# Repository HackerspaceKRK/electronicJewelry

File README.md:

electronicJewelry
=================

Electronic jewelry made for workshops on TEDx Kraków 2013

Dependencies:
arm-none-eabi toolchain

CodeSourcery toolchain:
http://www.mentor.com/embedded-software/sourcery-tools/sourcery-codebench/editions/lite-edition/
download EABI Release.

Compile with:
./do compile

and your .bin and .hex file is inside build/ directory

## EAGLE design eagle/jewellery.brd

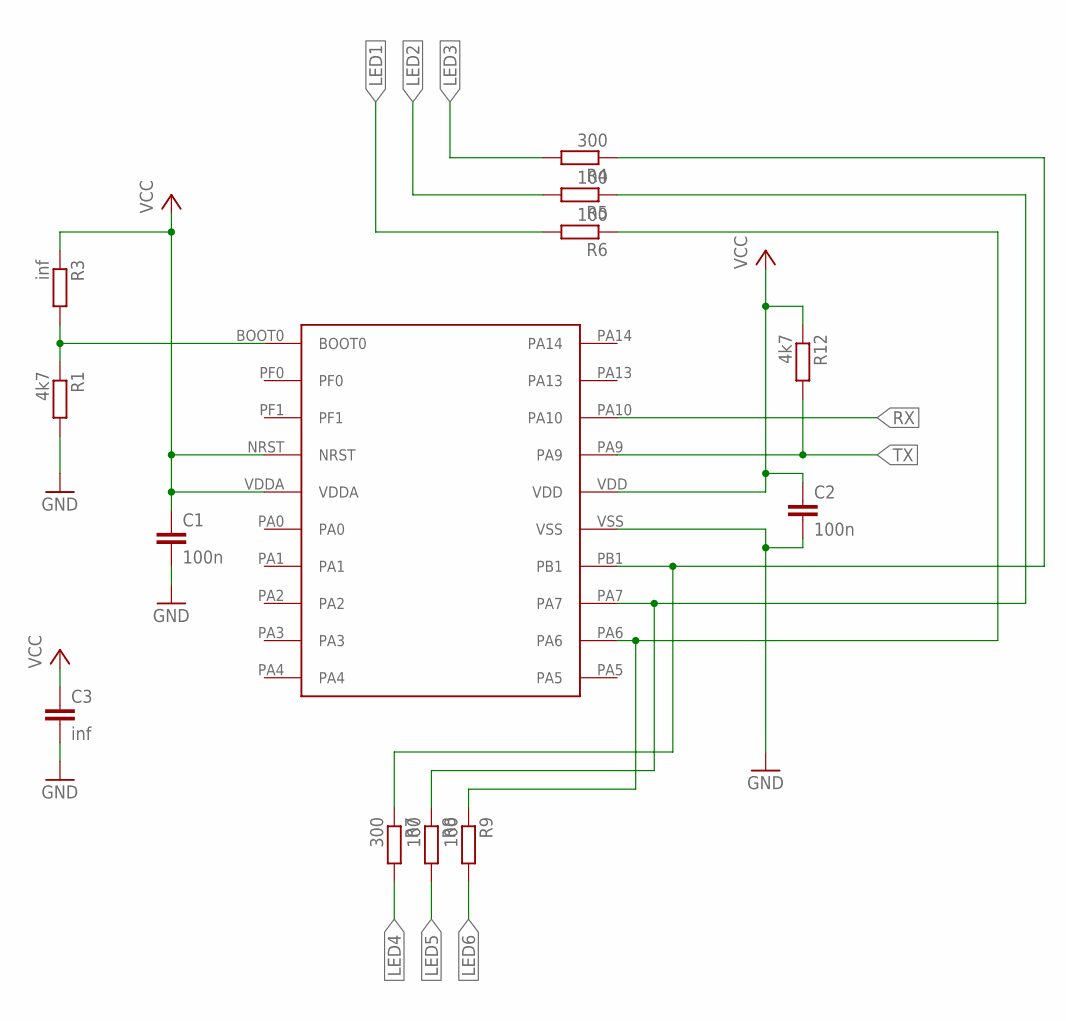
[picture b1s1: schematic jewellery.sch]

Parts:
C1, C2: 100n; C0805
C3: inf; C0805
R1, R12: 4k7; R0805
R3: inf; R0805
R4, R7: 300; R0805
R5, R6, R8, R9: 100; R0805
U$1: STM32F0; TSSOP20

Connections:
GND: C1.2, C2.2, C3.2, R1.2, U$1.VSS
LED1: R6.2
LED2: R5.2
LED3: R4.2
LED4: R7.2
LED5: R8.2
LED6: R9.2
unnamed: R1.1, R3.2, U$1.BOOT0
unnamed: R4.1, R7.1, U$1.PB1
unnamed: R5.1, R8.1, U$1.PA7
unnamed: R6.1, R9.1, U$1.PA6
RX: U$1.PA10
TX: R12.2, U$1.PA9
VCC: C1.1, C2.1, C3.1, R3.1, R12.1, U$1.NRST, U$1.VDD, U$1.VDDA

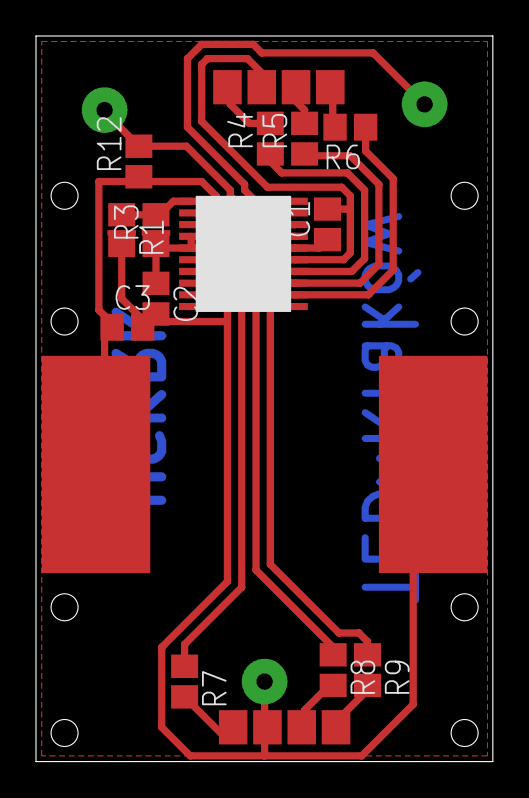
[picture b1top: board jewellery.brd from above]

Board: 2 copper layers, 25.4 x 40.3 mm, 13 parts (0 on the bottom side), 7 nets.

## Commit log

2013-11-09 ElectronicJewelry project files
2013-11-09 Link
